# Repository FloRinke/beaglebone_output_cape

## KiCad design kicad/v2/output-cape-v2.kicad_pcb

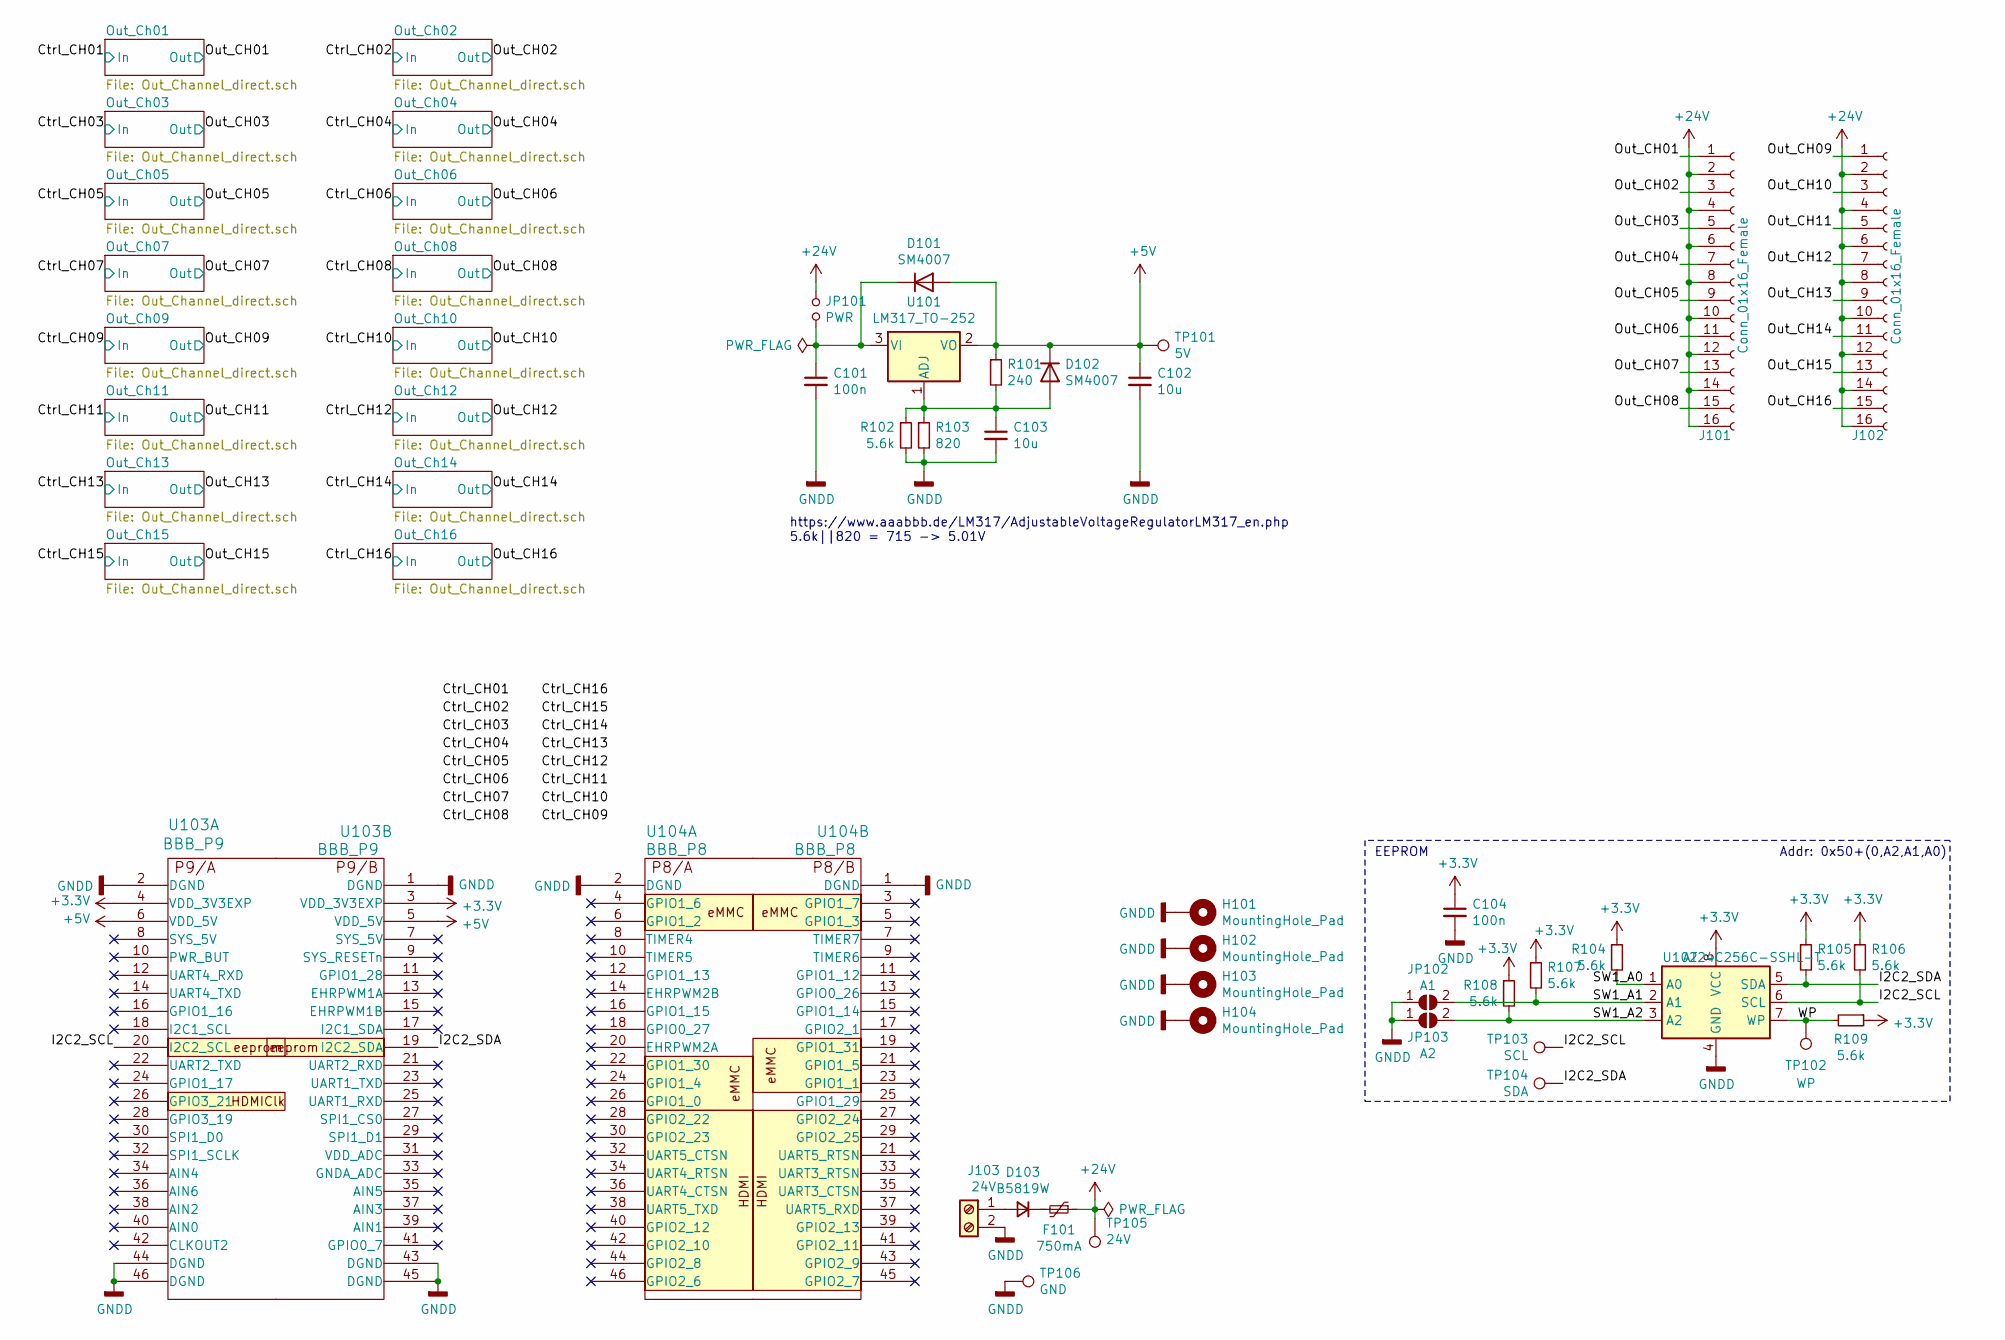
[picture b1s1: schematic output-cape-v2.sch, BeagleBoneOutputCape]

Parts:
C101, C104: 100n; C_0603_1608Metric; LCSC C14663
C102, C103: 10u; C_0402_1005Metric; LCSC C15525
D101, D102: SM4007; D_SOD-123F
D103: B5819W; D_SOD-123; LCSC C8598
F101: 750mA; Fuse_1812_4532Metric_Castellated; LCSC C12557
H101, H102, H103, H104: MountingHole_Pad; MountingHole_3.2mm_M3_ISO14580_Pad; JLCPCB BOM 0
J101, J102: Conn_01x16_Female; PhoenixContact_MC_1,5_16-G-3.5_1x16_P3.50mm_Horizontal; JLCPCB BOM 0
J103: 24V; PhoenixContact_MSTBA_2,5_2-G_1x02_P5.00mm_Horizontal; JLCPCB BOM 0
JP101: PWR; PinHeader_1x02_P1.27mm_Vertical; JLCPCB BOM 0
JP102: A1; SolderJumper-2_P1.3mm_Open_TrianglePad1.0x1.5mm; JLCPCB BOM 0
JP103: A2; SolderJumper-2_P1.3mm_Open_TrianglePad1.0x1.5mm; JLCPCB BOM 0
R101: 240; R_0603_1608Metric; LCSC C23350
R102, R104, R105, R106, R107, R108, R109: 5.6k; R_0402_1005Metric; LCSC C25908
R103: 820; R_0603_1608Metric; LCSC C23253
TP101: 5V; TestPoint_Keystone_5015_Micro-Minature; JLCPCB BOM 0
TP102: WP; TestPoint_Keystone_5015_Micro-Minature; JLCPCB BOM 0
TP103: SCL; TestPoint_Keystone_5015_Micro-Minature; JLCPCB BOM 0
TP104: SDA; TestPoint_Keystone_5015_Micro-Minature; JLCPCB BOM 0
TP105: 24V; TestPoint_Keystone_5015_Micro-Minature; JLCPCB BOM 0
TP106: GND; TestPoint_Keystone_5015_Micro-Minature; JLCPCB BOM 0
U101: LM317_TO-252; TO-252-2; LCSC C75510
U102: AT24C256C-SSHL-T; SOIC-8_3.9x4.9mm_P1.27mm; LCSC C6482
U103: BBB_P9; PinHeader_2x23_P2.54mm_Vertical_SMD; JLCPCB BOM 0
U104: BBB_P8; PinHeader_2x23_P2.54mm_Vertical_SMD; JLCPCB BOM 0

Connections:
+3V3: C104.1, R104.1, R105.1, R106.1, R107.1, R108.1, R109.1, U102.8 (VCC), U103.3 (VDD_3V3EXP), U103.4 (VDD_3V3EXP)
+5V: C102.1, D101.2 (A), D102.1 (K), R101.1, TP101.1, U101.2 (VO), U103.5 (VDD_5V), U103.6 (VDD_5V)
+24V: F101.1, J101.2, J101.4, J101.6, J101.8, J101.10, J101.12, J101.14, J101.16, J102.2, J102.4, J102.6, J102.8, J102.10, J102.12, J102.14, J102.16, JP101.1, TP105.1
/I2C2_SCL: R106.2, TP103.1, U102.6 (SCL), U103.20 (I2C2_SCL)
/I2C2_SDA: R105.2, TP104.1, U102.5 (SDA), U103.19 (I2C2_SDA)
/Out_CH01: J101.1; also elsewhere on the board
/Out_CH02: J101.3; also elsewhere on the board
/Out_CH03: J101.5; also elsewhere on the board
/Out_CH04: J101.7; also elsewhere on the board
/Out_CH05: J101.9; also elsewhere on the board
/Out_CH06: J101.11; also elsewhere on the board
/Out_CH07: J101.13; also elsewhere on the board
/Out_CH08: J101.15; also elsewhere on the board
/Out_CH09: J102.1; also elsewhere on the board
/Out_CH10: J102.3; also elsewhere on the board
/Out_CH11: J102.5; also elsewhere on the board
/Out_CH12: J102.7; also elsewhere on the board
/Out_CH13: J102.9; also elsewhere on the board
/Out_CH14: J102.11; also elsewhere on the board
/Out_CH15: J102.13; also elsewhere on the board
/Out_CH16: J102.15; also elsewhere on the board
/SW1_A0: R104.2, U102.1 (A0)
/SW1_A1: JP102.2 (B), R107.2, U102.2 (A1)
/SW1_A2: JP103.2 (B), R108.2, U102.3 (A2)
/WP: R109.2, TP102.1, U102.7 (WP)
GNDD: C101.2, C102.2, C103.2, C104.2, H101.1, H102.1, H103.1, H104.1, J103.2, JP102.1 (A), JP103.1 (A), R102.2, R103.2, TP106.1, U102.4 (GND), U103.1 (DGND), U103.2 (DGND), U103.43 (DGND), U103.44 (DGND), U103.45 (DGND), U103.46 (DGND), U104.1 (DGND), U104.2 (DGND); also elsewhere on the board
unnamed: C101.1, D101.1 (K), JP101.2, U101.3 (VI)
unnamed: C103.1, D102.2 (A), R101.2, R102.1, R103.1, U101.1 (ADJ)
unnamed: D103.1 (K), F101.2
unnamed: D103.2 (A), J103.1

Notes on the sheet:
EEPROM
https://www.aaabbb.de/LM317/AdjustableVoltageRegulatorLM317_en.php 5.6k||820 = 715 -> 5.01V
Addr: 0x50+(0,A2,A1,A0)

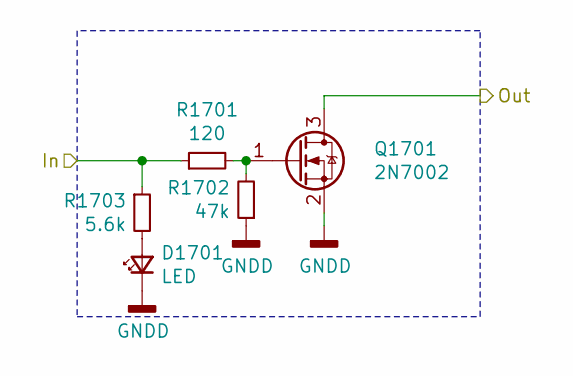
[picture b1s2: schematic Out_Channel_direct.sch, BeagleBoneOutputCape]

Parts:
D201: LED; LED_0603_1608Metric; LCSC C72043
Q201: 2N7002; SOT-23; LCSC C8545
R201: 120; R_0402_1005Metric; LCSC C25120
R202: 47k; R_0402_1005Metric; LCSC C25792
R203: 5.6k; R_0402_1005Metric; LCSC C25908

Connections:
/Ctrl_CH01: R201.1, R203.1
/Out_CH01: Q201.3 (D); also elsewhere on the board
GNDD: D201.1 (K), Q201.2 (S), R202.1; also elsewhere on the board
unnamed: D201.2 (A), R203.2
unnamed: Q201.1 (G), R201.2, R202.2

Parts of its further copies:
D301, D401, D501, D601, D701, D801, D901, D1001, D1101, D1201, D1301, D1401, D1501, D1601, D1701: LED; LED_0603_1608Metric; LCSC C72043
Q301, Q401, Q501, Q601, Q701, Q801, Q901, Q1001, Q1101, Q1201, Q1301, Q1401, Q1501, Q1601, Q1701: 2N7002; SOT-23; LCSC C8545
R301, R401, R501, R601, R701, R801, R901, R1001, R1101, R1201, R1301, R1401, R1501, R1601, R1701: 120; R_0402_1005Metric; LCSC C25120
R302, R402, R502, R602, R702, R802, R902, R1002, R1102, R1202, R1302, R1402, R1502, R1602, R1702: 47k; R_0402_1005Metric; LCSC C25792
R303, R403, R503, R603, R703, R803, R903, R1003, R1103, R1203, R1303, R1403, R1503, R1603, R1703: 5.6k; R_0402_1005Metric; LCSC C25908

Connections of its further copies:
/Ctrl_CH02: R301.1, R303.1
/Ctrl_CH03: R401.1, R403.1
/Ctrl_CH04: R501.1, R503.1
/Ctrl_CH05: R601.1, R603.1
/Ctrl_CH06: R701.1, R703.1
/Ctrl_CH07: R801.1, R803.1
/Ctrl_CH08: R901.1, R903.1
/Ctrl_CH09: R1001.1, R1003.1
/Ctrl_CH10: R1101.1, R1103.1
/Ctrl_CH11: R1201.1, R1203.1
/Ctrl_CH12: R1301.1, R1303.1
/Ctrl_CH13: R1401.1, R1403.1
/Ctrl_CH14: R1501.1, R1503.1
/Ctrl_CH15: R1601.1, R1603.1
/Ctrl_CH16: R1701.1, R1703.1
/Out_CH02: Q301.3 (D); also elsewhere on the board
/Out_CH03: Q401.3 (D); also elsewhere on the board
/Out_CH04: Q501.3 (D); also elsewhere on the board
/Out_CH05: Q601.3 (D); also elsewhere on the board
/Out_CH06: Q701.3 (D); also elsewhere on the board
/Out_CH07: Q801.3 (D); also elsewhere on the board
/Out_CH08: Q901.3 (D); also elsewhere on the board
/Out_CH09: Q1001.3 (D); also elsewhere on the board
/Out_CH10: Q1101.3 (D); also elsewhere on the board
/Out_CH11: Q1201.3 (D); also elsewhere on the board
/Out_CH12: Q1301.3 (D); also elsewhere on the board
/Out_CH13: Q1401.3 (D); also elsewhere on the board
/Out_CH14: Q1501.3 (D); also elsewhere on the board
/Out_CH15: Q1601.3 (D); also elsewhere on the board
/Out_CH16: Q1701.3 (D); also elsewhere on the board
GNDD: D301.1 (K), D401.1 (K), D501.1 (K), D601.1 (K), D701.1 (K), D801.1 (K), D901.1 (K), D1001.1 (K), D1101.1 (K), D1201.1 (K), D1301.1 (K), D1401.1 (K), D1501.1 (K), D1601.1 (K), D1701.1 (K), Q301.2 (S), Q401.2 (S), Q501.2 (S), Q601.2 (S), Q701.2 (S), Q801.2 (S), Q901.2 (S), Q1001.2 (S), Q1101.2 (S), Q1201.2 (S), Q1301.2 (S), Q1401.2 (S), Q1501.2 (S), Q1601.2 (S), Q1701.2 (S), R302.1, R402.1, R502.1, R602.1, R702.1, R802.1, R902.1, R1002.1, R1102.1, R1202.1, R1302.1, R1402.1, R1502.1, R1602.1, R1702.1; also elsewhere on the board
unnamed: D301.2 (A), R303.2
unnamed: D401.2 (A), R403.2
unnamed: D501.2 (A), R503.2
unnamed: D601.2 (A), R603.2
unnamed: D701.2 (A), R703.2
unnamed: D801.2 (A), R803.2
unnamed: D901.2 (A), R903.2
unnamed: D1001.2 (A), R1003.2
unnamed: D1101.2 (A), R1103.2
unnamed: D1201.2 (A), R1203.2
unnamed: D1301.2 (A), R1303.2
unnamed: D1401.2 (A), R1403.2
unnamed: D1501.2 (A), R1503.2
unnamed: D1601.2 (A), R1603.2
unnamed: D1701.2 (A), R1703.2
unnamed: Q301.1 (G), R301.2, R302.2
unnamed: Q401.1 (G), R401.2, R402.2
unnamed: Q501.1 (G), R501.2, R502.2
unnamed: Q601.1 (G), R601.2, R602.2
unnamed: Q701.1 (G), R701.2, R702.2
unnamed: Q801.1 (G), R801.2, R802.2
unnamed: Q901.1 (G), R901.2, R902.2
unnamed: Q1001.1 (G), R1001.2, R1002.2
unnamed: Q1101.1 (G), R1101.2, R1102.2
unnamed: Q1201.1 (G), R1201.2, R1202.2
unnamed: Q1301.1 (G), R1301.2, R1302.2
unnamed: Q1401.1 (G), R1401.2, R1402.2
unnamed: Q1501.1 (G), R1501.2, R1502.2
unnamed: Q1601.1 (G), R1601.2, R1602.2
unnamed: Q1701.1 (G), R1701.2, R1702.2

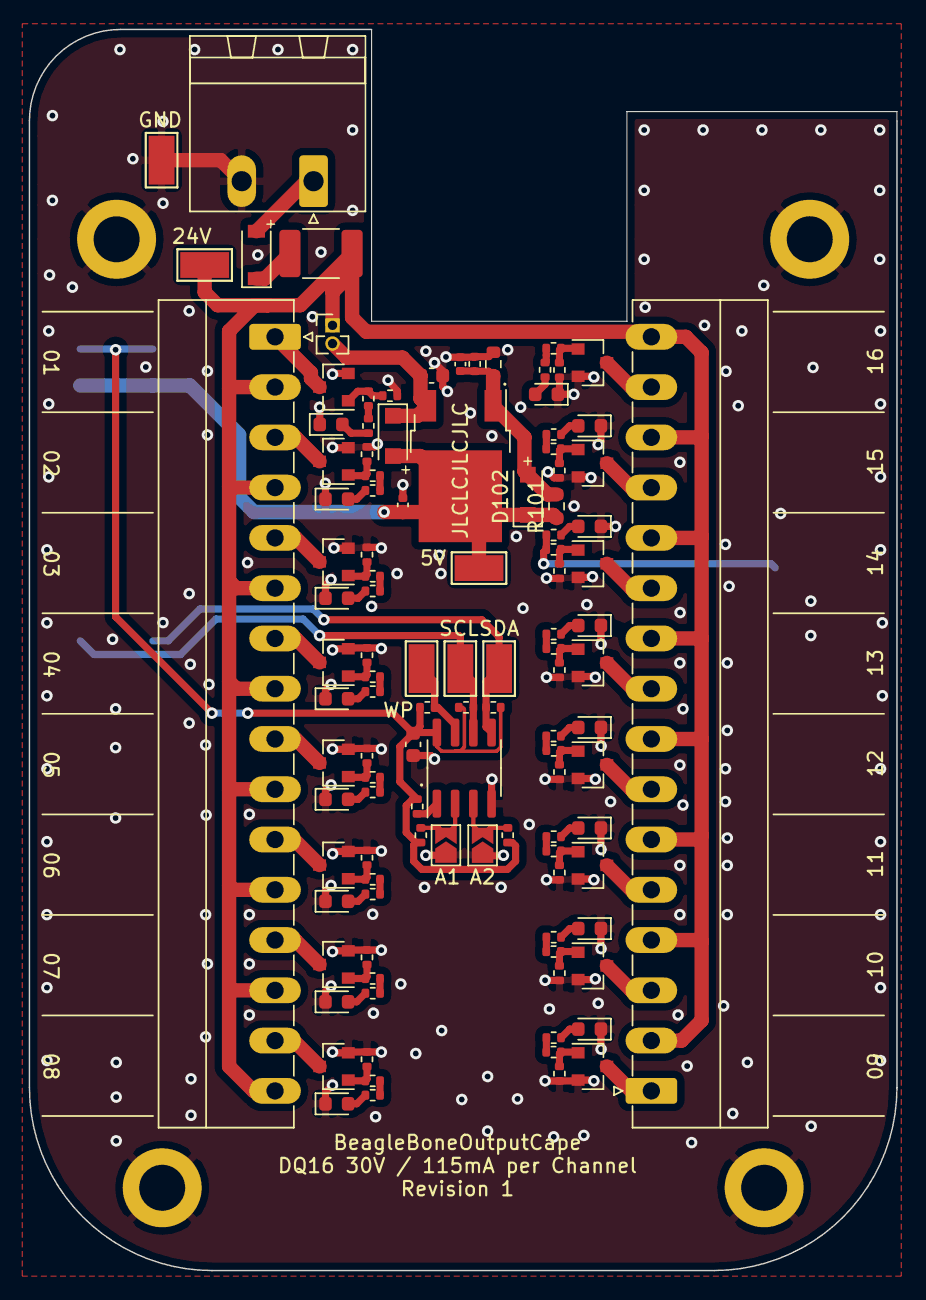
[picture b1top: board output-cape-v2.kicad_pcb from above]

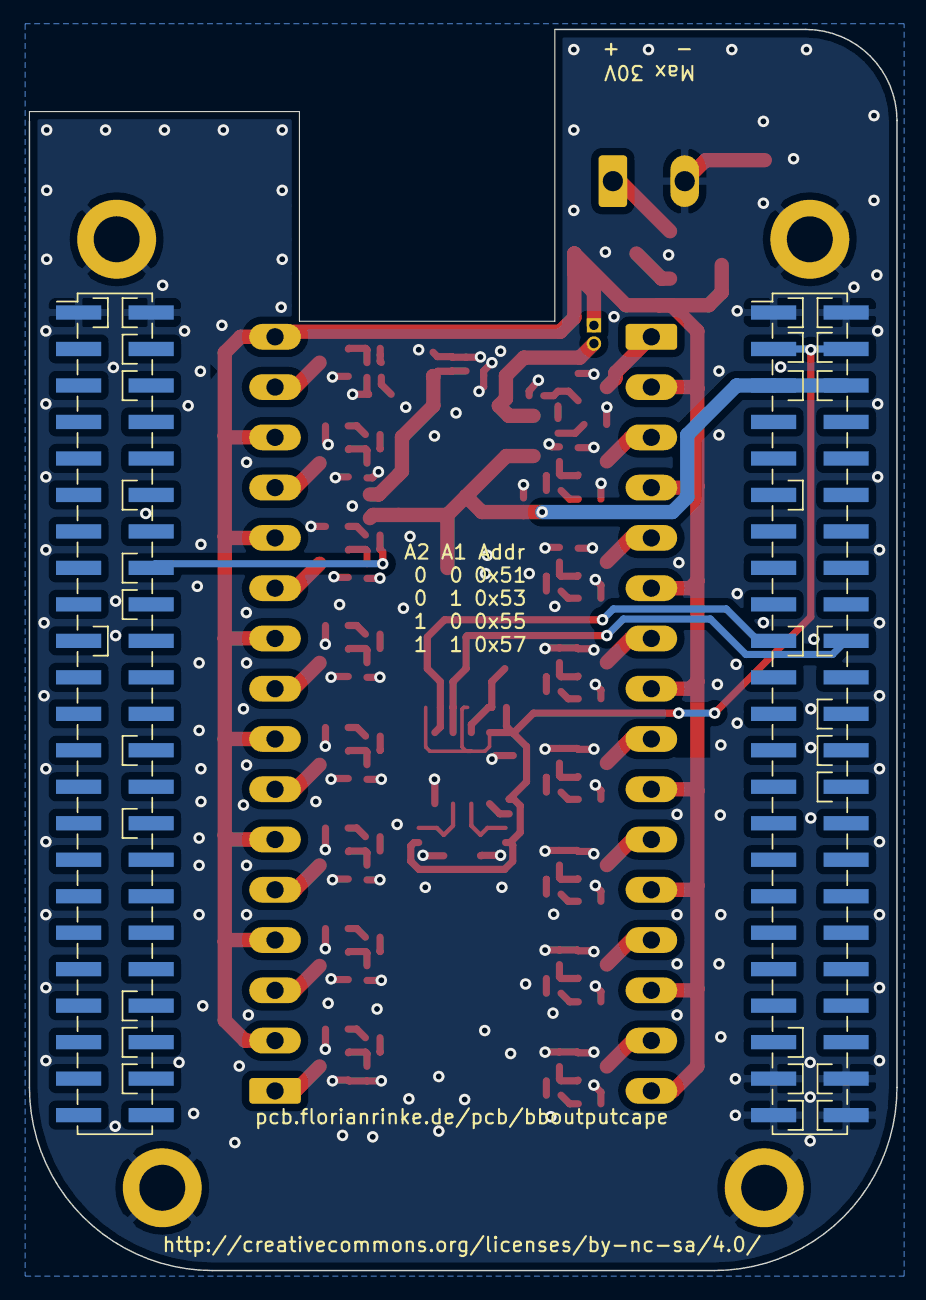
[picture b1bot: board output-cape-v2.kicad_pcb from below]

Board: 2 copper layers, 60.4 x 86.4 mm, 117 parts (2 on the bottom side), 78 nets.

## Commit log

2021-06-14 add revision 1
2021-06-14 add license file CC-BY-NC-SA
2021-06-19 add final V1 production files
2021-06-19 prepare repo for revision 1.1
2021-06-19 add git control files
2021-06-19 remove all pin assignments
    currently they some are colliding with internal use (eMMC, HDMI)

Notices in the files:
kicad/v2/Out_Channel_direct.sch:
http://creativecommons.org/licenses/by-nc-sa/4.0
